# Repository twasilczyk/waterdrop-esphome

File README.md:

# waterdrop-esphome

Smarten Waterdrop RO systems: a plug-in Wi-Fi add-on board to integrate with Home Assistant, read hidden diagnostic parameters, and work around refrigerator line limitations.

See the story: [Hacking a water filter through a 7-segment display](docs/story.md).

> [!WARNING]
> Use at your own risk. This is not a certified retail product, but an open-source hacking hobby project.

## Features

- Reads sensors exposed by original RO unit
  - Water TDS level
  - Individual filter state: total and remaining life plus derivative sensors (life percentage, filter health warning)
  - Pump state (idle, active, flushing)
  - Error codes
  - Ambient air temperature
  - Last filter change time
  - [Potentially more](docs/reverse-engineering.md), as about fourteen 16-bit fields are still not reverse-engineered
- Simulates faucet handle position (see [Refrigerator line workaround](#refrigerator-line-workaround))
- Switchable power supply to the main RO unit
- Emergency water shutoff with external latching solenoid valve

### Refrigerator line workaround

Waterdrop RO water filter systems don't play particularly well with refrigerator water lines. After dispensing water from the refrigerator, the RO unit tends to switch to an erratic flush mode: briefly flushing every 5 minutes. This continues until water is dispensed from the original Waterdrop smart faucet.

The simulated faucet handle feature works around this issue. If the RO unit performs this flush attempt while the faucet is reported open, it will start a proper flush cycle and switch back to the regular 12-hour flushing interval.

## Installing firmware

### ESPHome Builder

Best for long-term maintenance.

1. Define the following secrets (ESPHome Device Builder 🡒 three-dot menu 🡒 Secrets):
   - common_api_encryption_key
   - ota_password
   - wifi_ssid
   - wifi_password
2. Create device 🡒 Advanced set up options 🡒 Empty Configuration; paste the following:
   ```
   substitutions:
     branch: stable

   packages:
     waterdrop-esphome:
       url: https://github.com/twasilczyk/waterdrop-esphome
       ref: ${branch}
       files:
         - firmware/builder-package.yaml
   ```
3. Install over USB at first, then you can switch to OTA
4. If installing for the first time, don't forget to enable power to the RO system - it controlls both power supply and serial communication (with faucet as well as the main unit)

### Local environment

Best for development (from terminal or VSCode).

1. Set up ESPHome through the [pip method](https://esphome.io/guides/installing_esphome/#pip)
2. `cd path/to/repo`
3. `ln -s "$HOME/path/to/your/esphome-venv" .venv`
4. Create `secrets.yaml` one directory up from your repo root:
   ```
   wifi_ssid: "YourWiFi"
   wifi_password: "..."
   ota_password: "..."
   common_api_encryption_key: "..."
   ```

Then, you can build from terminal:
```
cd firmware
esphome run waterdrop-esphome.yaml
```

Or from VSCode:
1. Ctrl+Shift+P
2. `Tasks: Run Task`
3. `ESPHome: Run without debugging`

## Electronics

### Bill of materials

| Ref | Qty | Value     | Product          | Total cost [$] | Optional |
| --- | --- | --------- | ---------------- | -------------- | -------- |
| C1  | 1   | 100µF/50V | 50YXJ100M8X11.5  | 0.43 | |
| C2  | 1   | 220µF/16V | 25YXJ220M6.3X11  | 0.31 | |
| C3  | 1   | 22nF      | CL21B223KBANFNC  | 0.10 | |
| C4  | 1   | 100nF     | CL21B104KBCNNNC  | 0.10 | |
| D1  | 1   | SMAJ30A   | SMAJ30A          | 0.22 | |
| D2  | 1   | B360A     | B360A-13-F       | 0.51 | |
| D3  | 1   | 1N4148    | 1N4148W-7-F      | 0.17 | Yes (relay) |
| F1  | 1   | 500mA     | 0PTF0078P + 0217.500MXP | 1.35 <!-- 0.78 + 0.57 --> | |
| J1  | 1   | DC5525 m  | PJ-002B          | 0.66 | |
| J2  | 1   | DC5525 f  | 10-02950         | 3.17 | Yes (relay) |
| J3  | 1   |           | Waterdrop        | 0.00 | |
| J4  | 1   | 5pin 2.54 | PH1RB-05-UA      | 0.15 | |
| J5  | 1   | 2pin 2.54 | PH1RB-02-UA      | 0.10 | Yes (valve) |
| K1  | 1   | SPDT 24V  | G5LE-1-E DC24    | 2.74 | Yes (relay) |
| L1  | 1   | 33µH      | 12RS333C         | 1.35 | |
| L2  | 1   | 1µH       | MLZ2012A1R0WT000 | 0.10 | |
| Q1  | 1   | BC817     | BC817-40-7-F     | 0.23 | Yes (relay) |
| R1  | 1   | 3.6k      | 0805             | 0.10 | |
| R2  | 1   | 1.2k      | 0805             | 0.10 | |
| R3,R11 | 2 | 10k      | 0805             | 0.20 | R3 (relay) |
| R4  | 1   | 47k       | 0805             | 0.10 | Yes (relay) |
| R5,R6,R9,R13 | 4 | 100k | 0805           | 0.40 | R13 (valve) |
| R7,R10,R12 | 3 | 51k  | 0805             | 0.30 | R12 (valve) |
| R14 | 1   | 1Ω        | 0805             | 0.10 | Yes (valve) |
| U1  | 1   | LM2596DS-ADJ | LM2596DSADJG  | 2.34 | |
| U2  | 1   | ESP32-S3-Tiny | [ESP32-S3-Tiny-Kit](https://docs.waveshare.com/ESP32-S3-Tiny?variant=ESP32-S3-Tiny-Kit) | 11.99 | |
| U3  | 1   | 74AHCT125 | SN74AHCT125QDRQ1 | 0.70 | |
| U4  | 1   | TB67H450A | TB67H450AFNG     | 0.85 | Yes (valve) |
|     | 34  |           |                  | 28.87 | 21.11 w/o |

### Inlet water valve

Inlet water valve is an emergency shutoff valve for inlet water in case other components of your smart home detected a leak. However, I haven't had much luck finding one exactly matching my requirements:
 - Latching/pulse/bistable, so it doesn't take constant load (if Normally Closed) or wouldn't unintentionally re-open water flow in case of power loss (if Normally Open).
 - 3/8" Push-Fit connection to match RO system tubing.
 - Ideally 24V, to directly accept RO power supply voltage.
 - Reasonably priced.

A close one is SDF-S209B-24V, priced at $3.65 - but requires two G1/2 to Push-Fit 3/8 adapters. **24V latching solenoids are the only supported type of external inlet valves.**

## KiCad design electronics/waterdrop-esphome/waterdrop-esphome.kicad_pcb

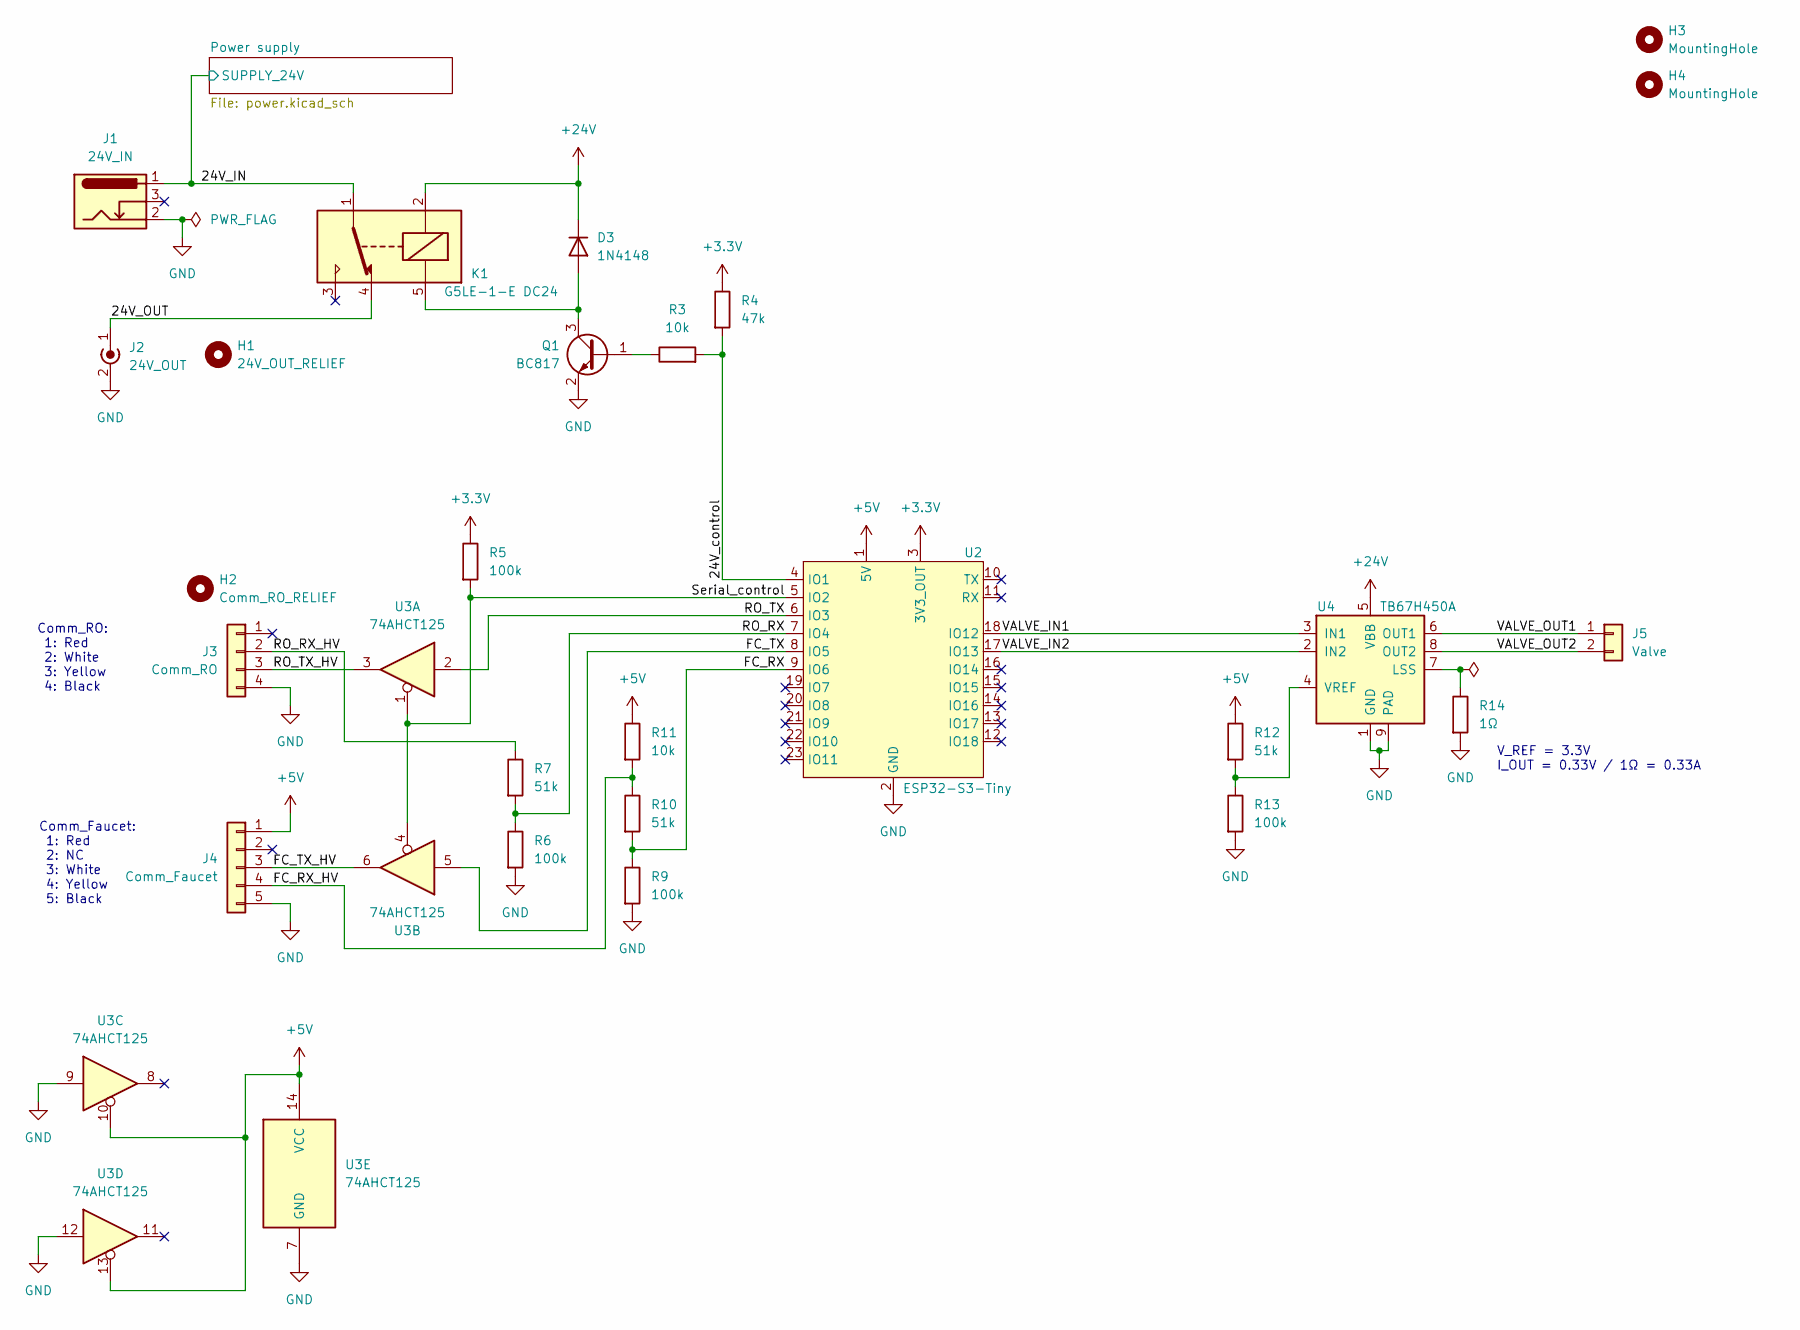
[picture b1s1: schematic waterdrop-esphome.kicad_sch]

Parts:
D3: 1N4148; D_SOD-123_Handsoldering
H1: 24V_OUT_RELIEF; MountingHole_4.3mm
H2: Comm_RO_RELIEF; MountingHole_4.3mm
H3, H4: MountingHole; MountingHole_3.2mm_M3
J1: 24V_IN; BarrelJack_Horizontal
J2: 24V_OUT; SolderWire-1.5sqmm_1x02_P6mm_D1.7mm_OD3mm_Relief
J3: Comm_RO; SolderWire-0.25sqmm_1x04_P4.2mm_D0.65mm_OD1.7mm_Relief
J4: Comm_Faucet; PinHeader_1x05_P2.54mm_Horizontal
J5: Valve; PinHeader_1x02_P2.54mm_Horizontal
K1: G5LE-1-E DC24; Relay_SPDT_Omron-G5LE-1
Q1: BC817; SOT-23_Handsoldering
R3, R11: 10k; R_0805_2012Metric_Pad1.20x1.40mm_HandSolder
R4: 47k; R_0805_2012Metric_Pad1.20x1.40mm_HandSolder
R5, R6, R9, R13: 100k; R_0805_2012Metric_Pad1.20x1.40mm_HandSolder
R7, R10, R12: 51k; R_0805_2012Metric_Pad1.20x1.40mm_HandSolder
R14: 1Ω; R_0805_2012Metric_Pad1.20x1.40mm_HandSolder
U2: ESP32-S3-Tiny; ESP32-S3-TINY-SMD
U3: 74AHCT125; SOIC-14_3.9x8.7mm_P1.27mm
U4: TB67H450A; SOIC-8-1EP_3.9x4.9mm_P1.27mm_EP2.29x3mm_ThermalVias

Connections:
+3.3V: R4.1, R5.1, U2.3 (3V3_OUT)
+5V: J4.1, R11.1, R12.1, U2.1 (5V), U3.10, U3.13, U3.14 (VCC); also elsewhere on the board
+24V: D3.1 (K), K1.2, U4.5 (VBB); also elsewhere on the board
/24V_IN: J1.1, K1.1; also elsewhere on the board
/24V_OUT: J2.1 (In), K1.4
/24V_control: R3.2, R4.2, U2.4 (IO1)
/FC_RX: R9.1, R10.2, U2.9 (IO6)
/FC_RX_HV: J4.4, R10.1, R11.2
/FC_TX: U2.8 (IO5), U3.5
/FC_TX_HV: J4.3, U3.6
/RO_RX: R6.1, R7.2, U2.7 (IO4)
/RO_RX_HV: J3.2, R7.1
/RO_TX: U2.6 (IO3), U3.2
/RO_TX_HV: J3.3, U3.3
/Serial_control: R5.2, U2.5 (IO2), U3.1, U3.4
/VALVE_IN1: U2.18 (IO12), U4.3 (IN1)
/VALVE_IN2: U2.17 (IO13), U4.2 (IN2)
/VALVE_OUT1: J5.1, U4.6 (OUT1)
/VALVE_OUT2: J5.2, U4.8 (OUT2)
GND: J1.2, J2.2 (Ext), J3.4, J4.5, Q1.2 (E), R6.2, R9.2, R13.2, R14.2, U2.2 (GND), U3.7 (GND), U3.9, U3.12, U4.1 (GND), U4.9 (PAD); also elsewhere on the board
unnamed: D3.2 (A), K1.5, Q1.3 (C)
unnamed: Q1.1 (B), R3.1
unnamed: R14.1, U4.7 (LSS)
unnamed: R12.2, R13.1, U4.4 (VREF)

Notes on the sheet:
Comm_Faucet: 1: Red 2: NC 3: White 4: Yellow 5: Black
Comm_RO: 1: Red 2: White 3: Yellow 4: Black
V_REF = 3.3V I_OUT = 0.33V / 1Ω = 0.33A

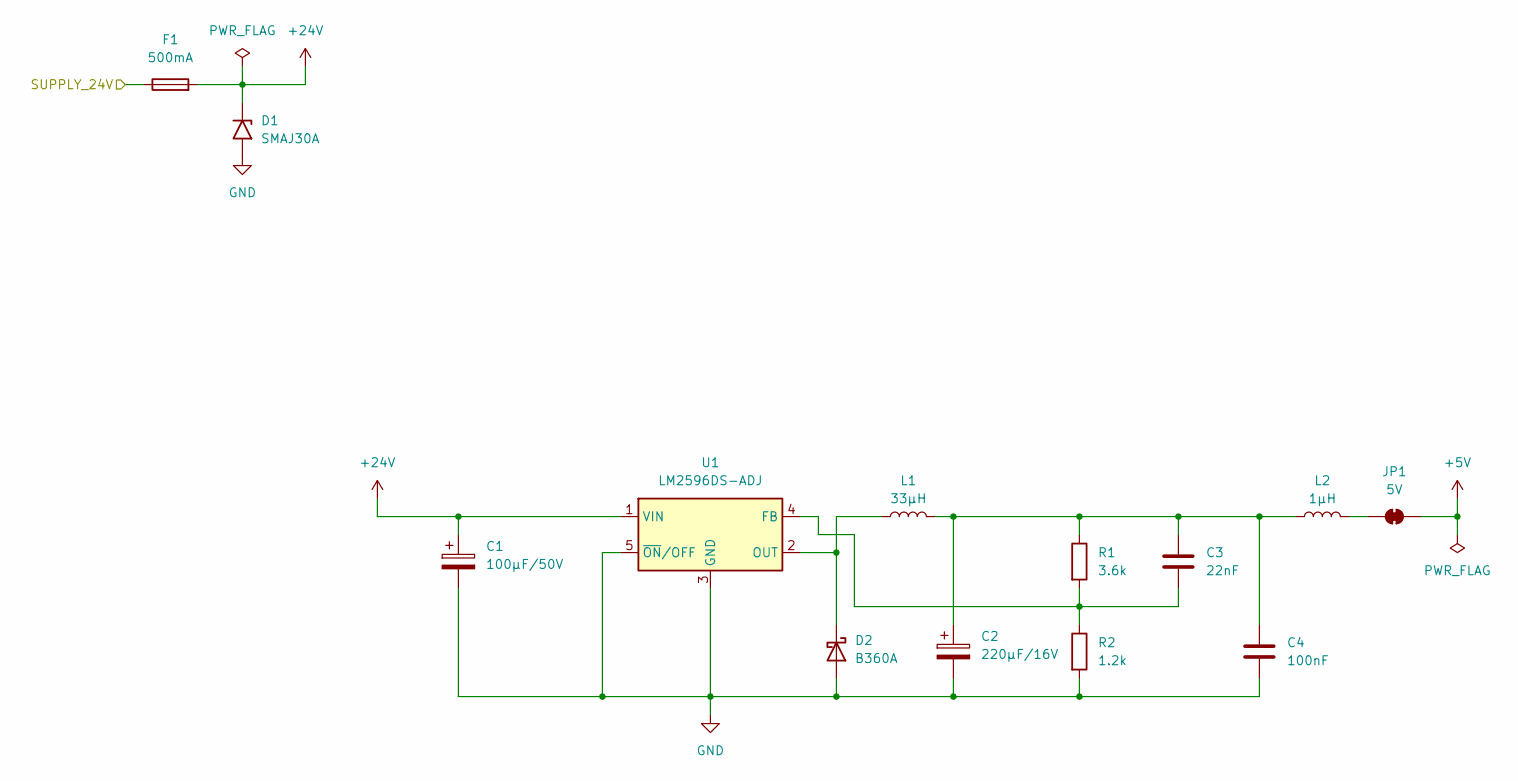
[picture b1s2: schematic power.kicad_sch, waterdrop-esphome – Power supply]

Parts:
C1: 100µF/50V; CP_Radial_D8.0mm_P3.50mm
C2: 220µF/16V; CP_Radial_D6.3mm_P2.50mm
C3: 22nF; C_0805_2012Metric_Pad1.18x1.45mm_HandSolder
C4: 100nF; C_0805_2012Metric_Pad1.18x1.45mm_HandSolder
D1: SMAJ30A; D_SMA_Handsoldering
D2: B360A; D_SMA_Handsoldering
F1: 500mA; Fuseholder_Cylinder-5x20mm_Stelvio-Kontek_PTF78_Horizontal_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
JP1: 5V; SolderJumper-2_P1.3mm_Bridged_Pad1.0x1.5mm
L1: 33µH; L_Radial_D10.5mm_P4.00x5.00mm_Murata_1200RS
L2: 1µH; L_0805_2012Metric_Pad1.15x1.40mm_HandSolder
R1: 3.6k; R_0805_2012Metric_Pad1.20x1.40mm_HandSolder
R2: 1.2k; R_0805_2012Metric_Pad1.20x1.40mm_HandSolder
U1: LM2596DS-ADJ; TO-263-5_TabPin3

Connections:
+5V: JP1.2 (B); also elsewhere on the board
+24V: C1.1, D1.1 (A1), F1.2, U1.1 (VIN); also elsewhere on the board
/24V_IN: F1.1; also elsewhere on the board
GND: C1.2, C2.2, C4.2, D1.2 (A2), D2.2 (A), R2.2, U1.3 (GND), U1.5 (~ON/OFF); also elsewhere on the board
unnamed: C2.1, C3.1, C4.1, L1.2, L2.1, R1.1
unnamed: D2.1 (K), L1.1, U1.2 (OUT)
unnamed: JP1.1 (A), L2.2
unnamed: C3.2, R1.2, R2.1, U1.4 (FB)

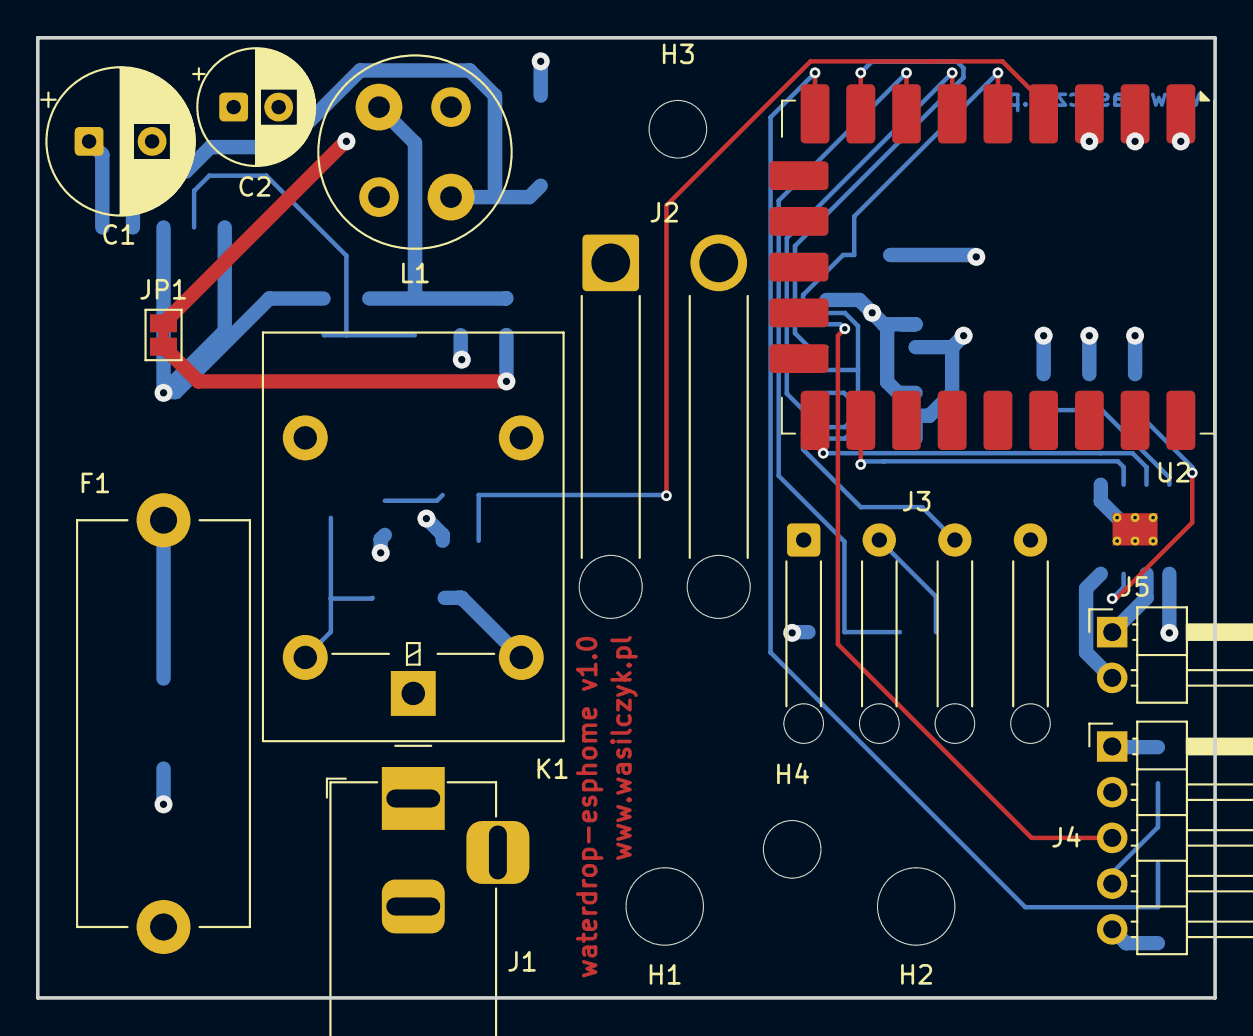
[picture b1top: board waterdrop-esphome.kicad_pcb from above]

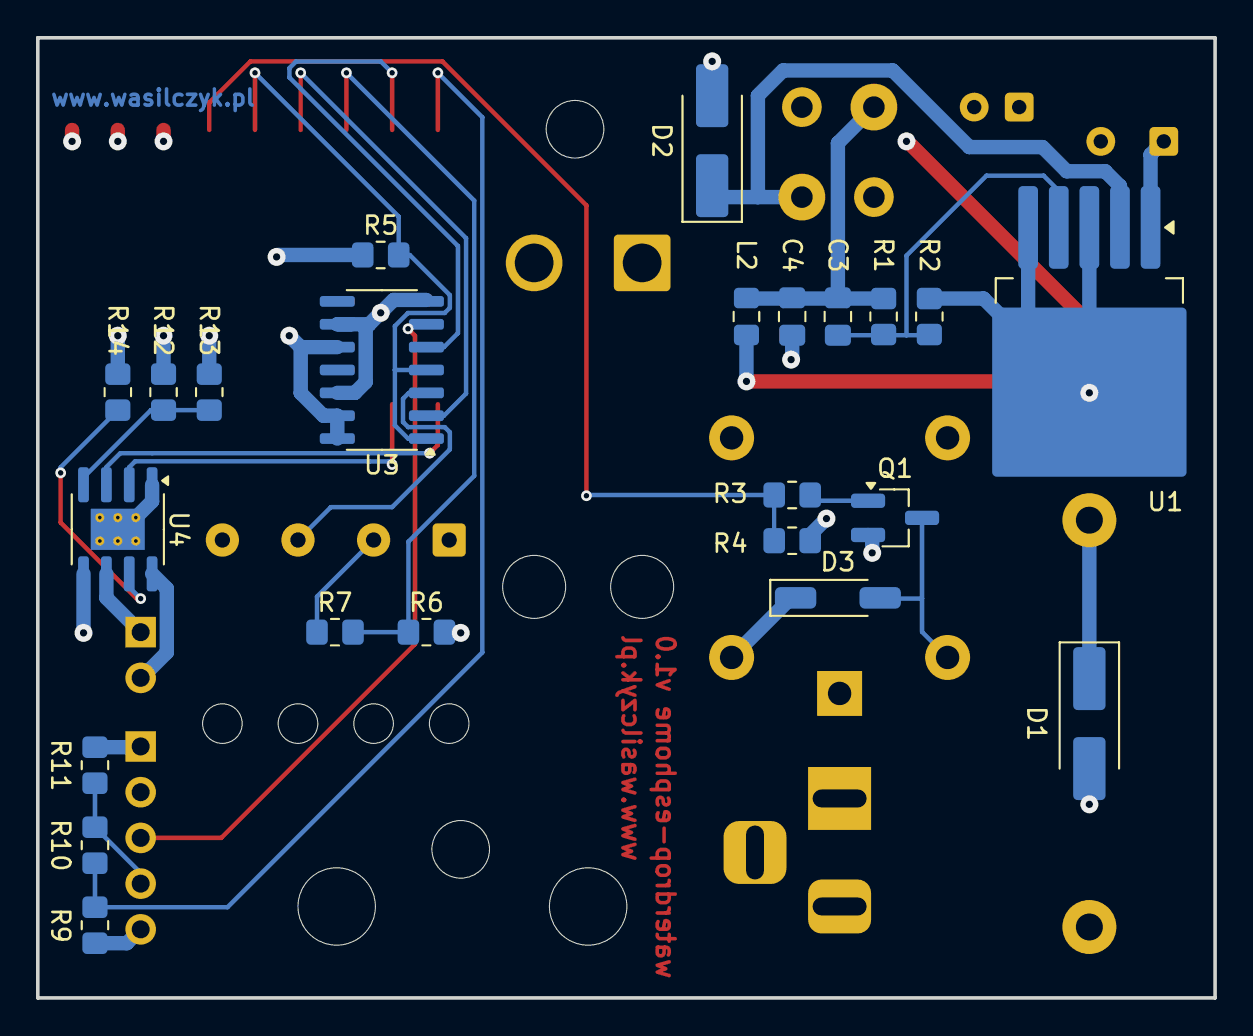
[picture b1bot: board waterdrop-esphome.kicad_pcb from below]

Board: 4 copper layers, 65.4 x 53.3 mm, 39 parts (23 on the bottom side), 28 nets.

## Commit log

2025-12-15 Bring up prototype board
2026-01-03 Replay regular use
2026-01-03 Figured out filter usage
2026-01-06 Figured out flush
2026-01-06 Figured out status message
2026-01-09 Found TDS F-codes and buffer overrun
2026-01-09 Found filter life length config
2026-01-10 Discovered protocol cycles
2026-01-13 Initial schematics and pcb
2026-01-13 ESP32-S3-Tiny doesn't have dual-purpose power pins, it requires 5V supply
2026-03-12 Schematics for 12V circuit, describe serial level converter
2026-03-14 Schematics for serial communication
2026-03-14 Schematics for water valve
2026-03-14 Schematics are ready for PCB layout
2026-03-15 PCB: lay out components
2026-03-27 PCB: trace and fix all DRC
2026-03-27 PCB: release settings
2026-03-27 PCB: add signature
2026-04-12 Firmware: update GPIO for 0.0.1 board
2026-04-12 Setup environment for VS Code
2026-04-13 Firmware: implement bi-stable valve
2026-04-18 Firmware cleanup
2026-04-21 Serial protocol: implement RO frames receiver
2026-04-25 Enable more warnings
2026-04-25 Serial protocol: implement sending faucet frames
2026-04-26 Serial protocol: implement faucet frames receiver
2026-05-03 Serial protocol: RO communication loop
2026-05-03 Serial protocol: ensure frame separation
2026-05-03 Serial protocol: implement faucet request command
2026-05-11 Serial protocol: introduce Message
2026-05-11 Message as packed_variant
2026-05-12 waterdrop_serial: minor class cleanup
2026-05-13 Serial protocol: better representation (big_uint16_t and Frame::as)
2026-05-14 Clean up old diagnostic sensors
2026-05-15 Expose serial data through sensors
2026-05-15 Add more entities: booting, flushing, errors, faucet state
2026-05-15 Add diagnostic byte sensors
2026-05-15 Tweak power and status icons
2026-05-16 Add unexpected frame sensor
2026-05-18 Serial protocol reverse engineering: update sensors for unknown values
2026-05-19 Discovered total hours powered on sensor
2026-05-19 Implement request_unknown_values, reverse engineer what else faucet can do
2026-05-21 Message22Slot05
2026-05-21 Simplify request_unknown_values
2026-05-21 Booting sensor was wrong, introduce pump active
2026-05-21 Avoid RO leeching power from serial when turned off
2026-05-21 report_unknown_values disables raw bytes reporting
2026-05-30 Article about reverse-engineering story
2026-05-31 Schematics: apply verified 0.1 fixes: - Bump version to 0.2 - Change mounting holes to M3 - 12 -> 24V input voltage: - C1: 16V -> 50V - D1: SMAJ13A -> SMAJ30A - D2: B220A -> B360A - K1: G5LE-1 -> G5L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
2026-06-04 Story: add some links to code
2026-06-05 Remove R8: Serial RX pull-up from RO unit
    It's only necessary for faucet. Without this pull-up, this module already
    performs better than original faucet. Rising and falling edge comparison
    (+/- 10ns, except faucet rising edge):
    - 560ns with waterdrop-esphome (both RX and TX, both edges)
    - 620ns with original faucet (RO side, both edges)
    - 640ns with original faucet (faucet side, falling edge)
2026-06-06 Filter remaining life can go negative
2026-06-06 Remember simulated faucet state across reboots
2026-06-07 Update footprints: D3 and Q1 hand soldering, C1 size
2026-06-07 Document BOM
2026-06-07 Bump PCB version to 0.2
2026-06-07 Update PCB to reflect schematic fixes
2026-06-07 Fix PCB 0.1 nits
2026-06-07 Refine README
2026-06-23 Discovered ambient air temperature
2026-06-23 Fix board strings
2026-06-23 Introduce ESPHome Builder compatibility
2026-06-24 Move faucet_open switch to config category
2026-06-24 Fix status LED priorities
2026-06-24 Don't drop valve open/close requests if they were made during cooldown period
2026-06-26 Expose request/report unknown values as substitutions
2026-06-27 Story: update photos/screenshots
2026-06-27 Inlet water valve: rename and document
2026-06-28 Raw byte -> Unknown sensor
2026-06-28 Protocol reverse engineering around filter replacement - MagicSensor1 - Expose all 4 temperature sensors - Note down state observations - Operating lifetime -> Last filter change - Correct article
2026-06-29 Move Reverse-engineering notes to separate doc
2026-06-29 Fix pre-release nits
2026-06-29 Bump PCB version to 1.0 and firmware to 1.0.0
